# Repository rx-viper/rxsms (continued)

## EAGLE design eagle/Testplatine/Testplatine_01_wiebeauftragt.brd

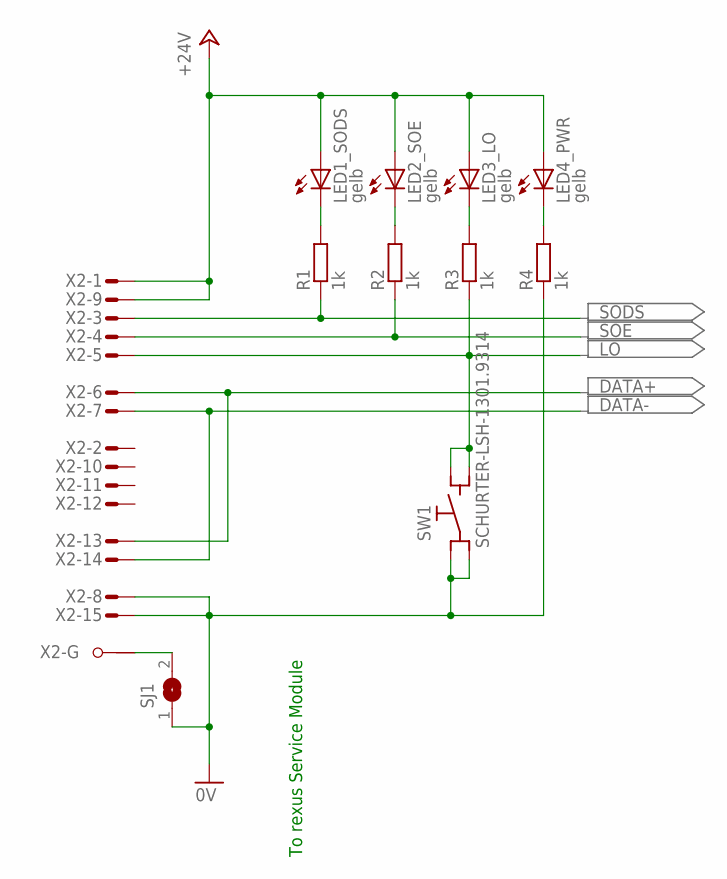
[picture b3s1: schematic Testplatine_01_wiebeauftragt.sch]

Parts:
LED1_SODS, LED2_SOE, LED3_LO, LED4_PWR: gelb; CHIPLED_0805
R1, R2, R3, R4: 1k; R0805
SJ1: SJ
SW1: SCHURTER-LSH-1301.9314; LSH
X2: M15HPS; M15HP

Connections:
0V: R4.1, SJ1.1, SW1.C1 (C), SW1.C2 (C), X2.8 (M), X2.15 (M)
+24V: LED1_SODS.A, LED2_SOE.A, LED3_LO.A, LED4_PWR.A, X2.1 (M), X2.9 (M)
DATA+: X2.6 (M), X2.13 (M)
DATA-: X2.7 (M), X2.14 (M)
LO: R3.1, SW1.NO1 (NO), SW1.NO2 (NO), X2.5 (M)
unnamed: LED1_SODS.C, R1.2
unnamed: LED2_SOE.C, R2.2
unnamed: LED3_LO.C, R3.2
unnamed: LED4_PWR.C, R4.2
unnamed: SJ1.2, X2.G1
SODS: R1.1, X2.3 (M)
SOE: R2.1, X2.4 (M)

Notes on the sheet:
To rexus Service Module

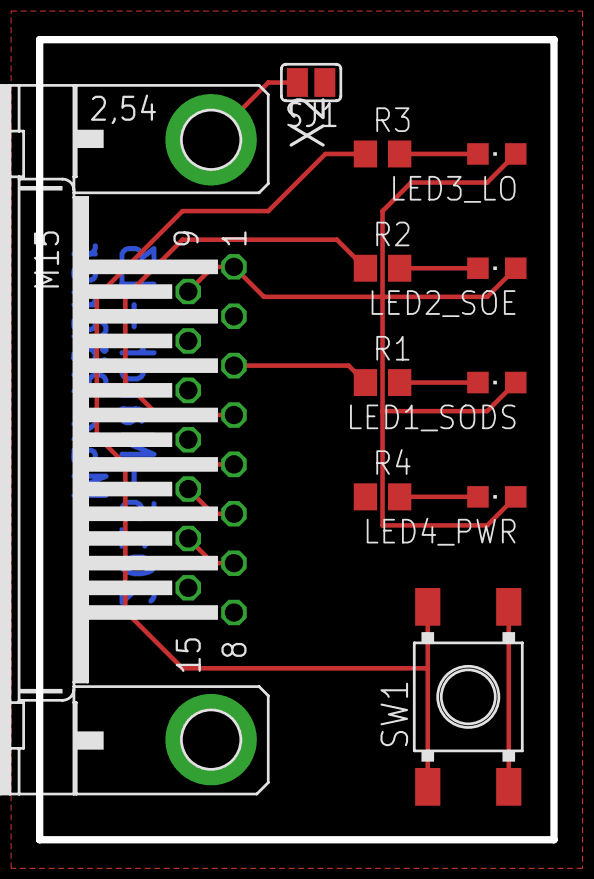
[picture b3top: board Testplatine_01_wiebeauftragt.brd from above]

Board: 2 copper layers, 28.6 x 44.5 mm, 11 parts (0 on the bottom side), 12 nets.

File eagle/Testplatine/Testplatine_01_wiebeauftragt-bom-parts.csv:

"Part";"Value";"Device";"Package";"Description";"MF";"MPN";"OC_FARNELL";"OC_NEWARK";"OC_RS";
"LED1_SODS";"gelb";"LEDCHIPLED_0805";"CHIPLED_0805";"LED";"";"";"2099242";"";"";
"LED2_SOE";"gelb";"LEDCHIPLED_0805";"CHIPLED_0805";"LED";"";"";"2099242";"";"";
"LED3_LO";"gelb";"LEDCHIPLED_0805";"CHIPLED_0805";"LED";"";"";"2099242";"";"";
"LED4_PWR";"gelb";"LEDCHIPLED_0805";"CHIPLED_0805";"LED";"";"";"2099242";"";"";
"R1";"1k";"R-EU_R0805";"R0805";"RESISTOR, European symbol";"";"";"1887280";"";"";
"R2";"1k";"R-EU_R0805";"R0805";"RESISTOR, European symbol";"";"";"1887280";"";"";
"R3";"1k";"R-EU_R0805";"R0805";"RESISTOR, European symbol";"";"";"1887280";"";"";
"R4";"1k";"R-EU_R0805";"R0805";"RESISTOR, European symbol";"";"";"1887280";"";"";
"SJ1";"";"SJ";"SJ";"SMD solder JUMPER";"";"";"";"";"";
"SW1";"SCHURTER-LSH-1301.9314";"SCHURTER-LSH-1301.9314";"LSH";"Schurter LSH Printmount Switches, Gullwing Leads [SMT]";"";"";"1217763";"";"";
"X2";"";"M15HPS";"M15HP";"SUB-D";"";"";"1097065 + 2x 1855027";"unknown";"692-7976 + 2x 719-9753";

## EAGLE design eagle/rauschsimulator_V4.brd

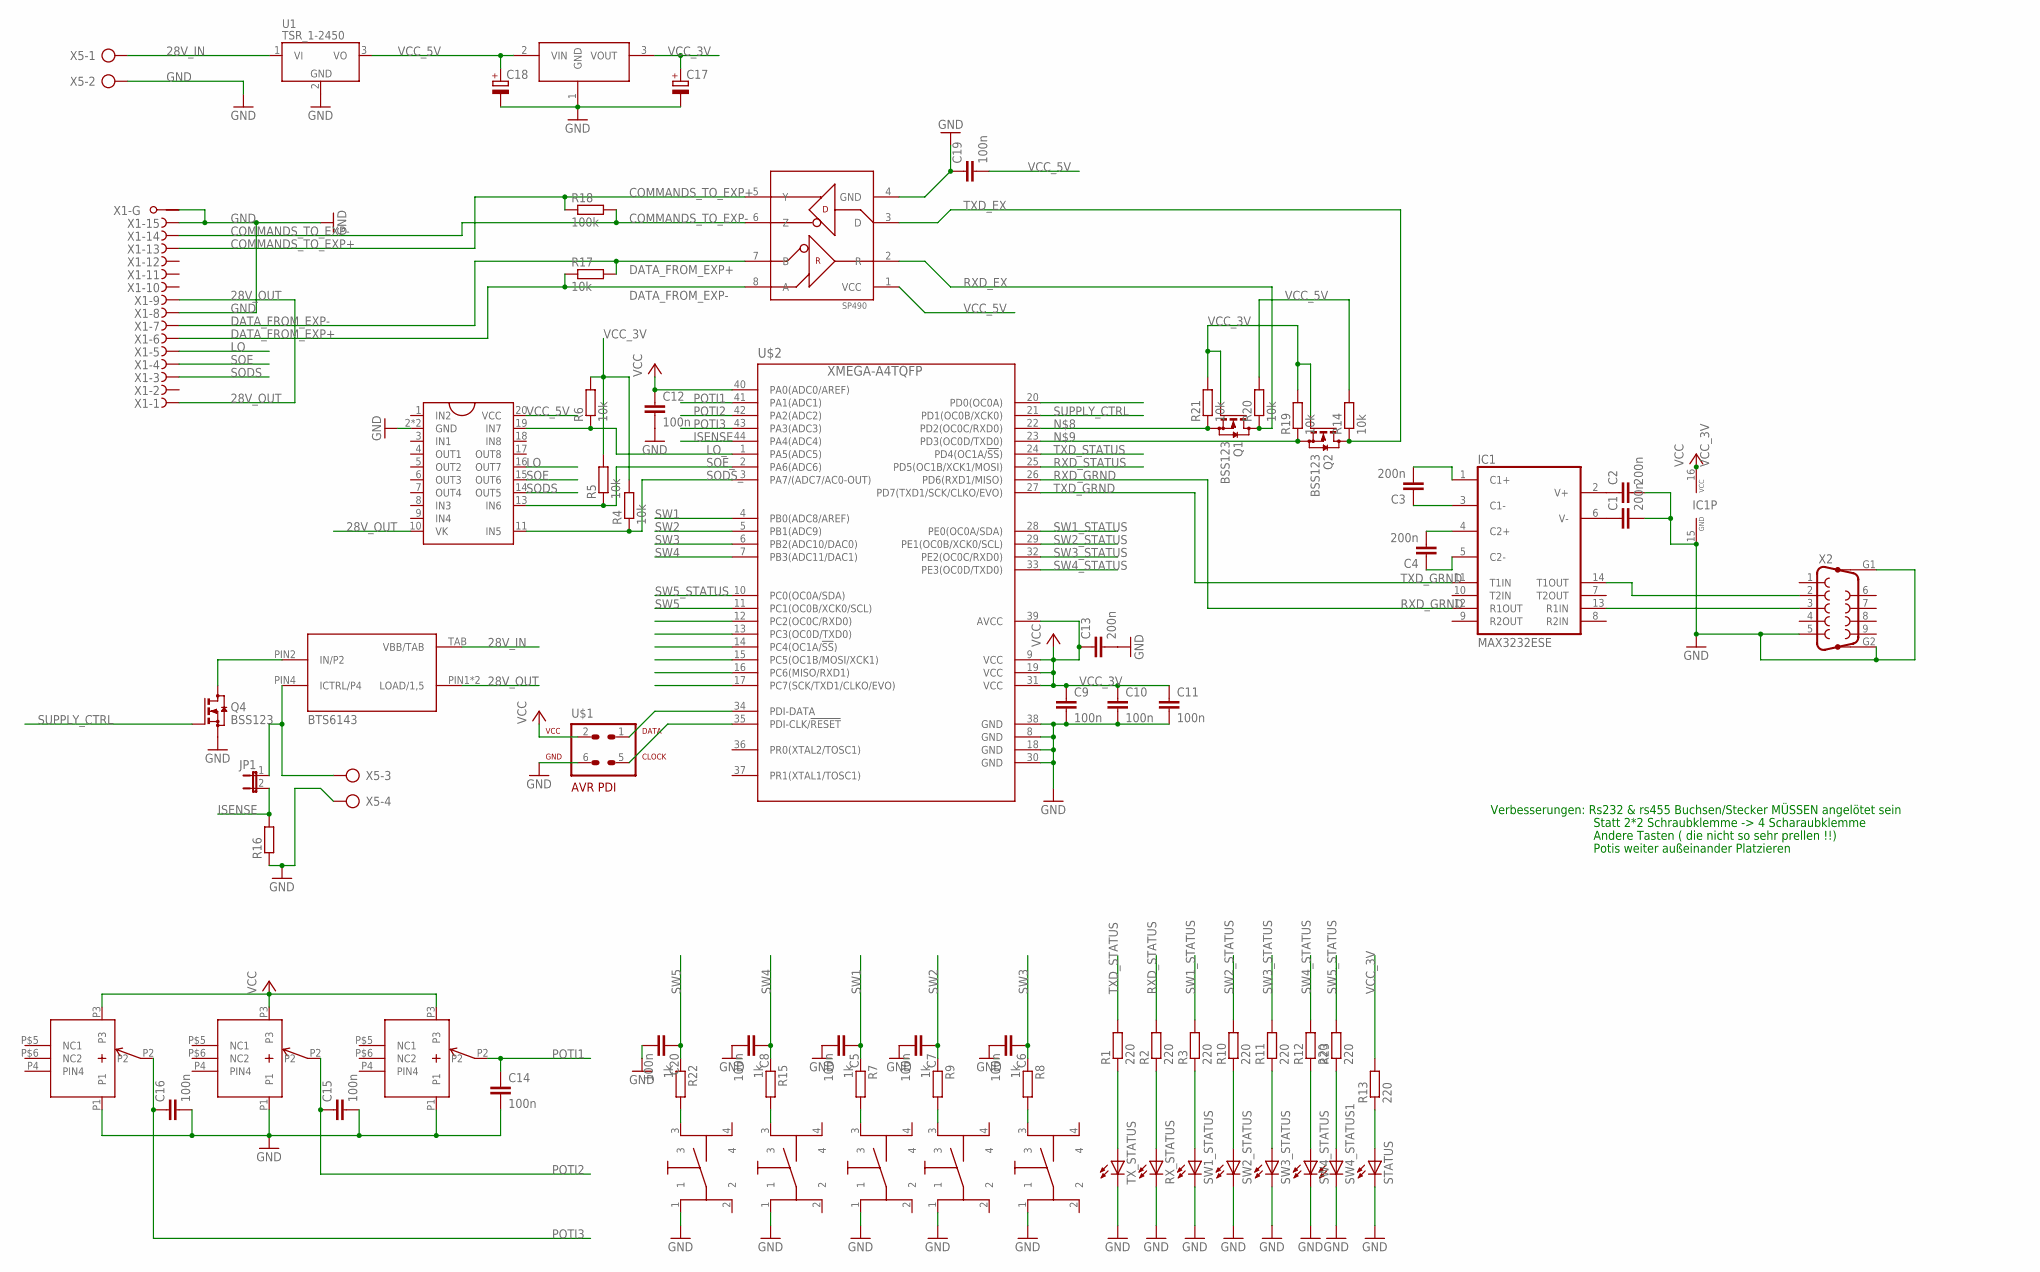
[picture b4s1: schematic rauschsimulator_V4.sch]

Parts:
C1, C2, C3, C4, C13: 200n; C0603K
C5, C6, C7, C8, C9, C10, C11, C12, C14, C15, C16, C19, C20: 100n; C0603K
C17, C18: CPOL-EUE2.5-6; E2,5-6
IC1: MAX3232ESE; SO16
JP1: JP1E; JP1
Q1, Q2, Q4: BSS123; SOT23
R1, R2, R3, R10, R11, R12, R13, R23: 220; R0603
R4, R5, R6, R14, R17, R19, R20, R21: 10k; R0603
R7, R8, R9, R15, R22: 1k; R0603
R16: R-EU_0617/22; 0617/22
R18: 100k; R0603
RX_STATUS: LEDCHIPLED_1206; CHIPLED_1206
STATUS: LEDCHIPLED_1206; CHIPLED_1206
SW1, SW2, SW3, SW4, SW5: SMS_IP67; IP67
SW1_STATUS, SW2_STATUS, SW3_STATUS, SW4_STATUS, SW4_STATUS1: LEDCHIPLED_1206; CHIPLED_1206
TX_STATUS: LEDCHIPLED_1206; CHIPLED_1206
U1: TSR_1-2450; TSR-1
U$1: AVR-PDIVERT; AVR-ISP-6
U$2: XMEGA-A4TQFP; TQFP44
U$3, U$4, U$5: STRK11K; VERT_POTI
U$13: LM1117; TO252
U$14: BTS6143; TO-252-5-1
U$15: UDN2596; DIL20
U$16: SP490; SO08
X1: F15HPS; F15HP
X2: F09HP
X5: AK500/4

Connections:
28V_IN: U1.1 (VI), U$14.TAB (VBB/TAB), X5.1
28V_OUT: U$14.PIN1 (LOAD/1,5), U$14.PIN5 (LOAD/1,5), U$15.10 (VK), X1.1 (F), X1.9 (F)
COMMANDS_TO_EXP+: R18.1, U$16.5 (Y), X1.13 (F)
COMMANDS_TO_EXP-: R18.2, U$16.6 (Z), X1.14 (F)
DATA_FROM_EXP+: R17.1, U$16.8 (A), X1.6 (F)
DATA_FROM_EXP-: R17.2, U$16.7 (B), X1.7 (F)
GND: C1.2, C2.2, C5.2, C6.2, C7.2, C8.2, C9.2, C10.2, C11.2, C12.2, C13.2, C14.2, C15.2, C16.2, C17.-, C18.-, C19.1, C20.2, IC1.15 (GND), Q4.2 (S), R16.1, RX_STATUS.C, STATUS.C, SW1.1, SW1_STATUS.C, SW2.1, SW2_STATUS.C, SW3.1, SW3_STATUS.C, SW4.1, SW4_STATUS.C, SW4_STATUS1.C, SW5.1, TX_STATUS.C, U1.2 (GND), U$1.6, U$2.8 (GND), U$2.18 (GND), U$2.30 (GND), U$2.38 (GND), U$3.P1, U$4.P1, U$5.P1, U$13.1 (GND), U$15.2 (GND), U$15.12 (GND), U$16.4 (GND), X1.8 (F), X1.15 (F), X1.G1, X2.5, X2.G1, X2.G2, X5.2, X5.4
ISENSE: JP1.2, R16.2, U$2.44 (PA4(ADC4))
LO: U$15.16 (OUT7), X1.5 (F)
LO_: R6.1, U$2.1 (PA5(ADC5)), U$15.19 (IN7)
unnamed: C1.1, IC1.6 (V-)
unnamed: C2.1, IC1.2 (V+)
unnamed: C4.2, IC1.4 (C2+)
unnamed: C4.1, IC1.5 (C2-)
unnamed: C3.1, IC1.3 (C1-)
unnamed: C3.2, IC1.1 (C1+)
unnamed: U$1.1, U$2.34 (PDI-DATA)
unnamed: Q1.2 (S), R21.1, U$2.22 (PD2(OC0C/RXD0))
unnamed: Q2.2 (S), R19.1, U$2.23 (PD3(OC0D/TXD0))
unnamed: IC1.13 (R1IN), X2.3
unnamed: R8.2, SW1.3
unnamed: IC1.14 (T1OUT), X2.2
unnamed: R9.2, SW2.3
unnamed: R7.2, SW3.3
unnamed: U$1.5, U$2.35 (PDI-CLK/!RESET)
unnamed: Q4.3 (D), U$14.PIN2 (IN/P2)
unnamed: R10.1, SW2_STATUS.A
unnamed: R1.1, TX_STATUS.A
unnamed: R2.1, RX_STATUS.A
unnamed: R3.1, SW1_STATUS.A
unnamed: R11.1, SW3_STATUS.A
unnamed: R12.1, SW4_STATUS.A
unnamed: R13.1, STATUS.A
unnamed: R15.2, SW4.3
unnamed: R23.1, SW4_STATUS1.A
unnamed: JP1.1, U$14.PIN4 (ICTRL/P4), X5.3
unnamed: R22.2, SW5.3
POTI1: C14.1, U$2.41 (PA1(ADC1)), U$5.P2
POTI2: C15.1, U$2.42 (PA2(ADC2)), U$4.P2
POTI3: C16.1, U$2.43 (PA3(ADC3)), U$3.P2
RXD_EX: Q1.3 (D), R20.1, U$16.2 (R)
RXD_GRND: IC1.12 (R1OUT), U$2.26 (PD6(RXD1/MISO))
RXD_STATUS: R2.2, U$2.25 (PD5(OC1B/XCK1/MOSI))
SODS: U$15.14 (OUT5), X1.3 (F)
SODS_: R4.1, U$2.3 (PA7/(ADC7/AC0-OUT)), U$15.11 (IN5)
SOE: U$15.15 (OUT6), X1.4 (F)
SOE_: R5.1, U$2.2 (PA6(ADC6)), U$15.13 (IN6)
SUPPLY_CTRL: Q4.1 (G), U$2.21 (PD1(OC0B/XCK0))
SW1: C5.1, R7.1, U$2.4 (PB0(ADC8/AREF))
SW1_STATUS: R3.2, U$2.28 (PE0(OC0A/SDA))
SW2: C7.1, R9.1, U$2.5 (PB1(ADC9))
SW2_STATUS: R10.2, U$2.29 (PE1(OC0B/XCK0/SCL))
SW3: C6.1, R8.1, U$2.6 (PB2(ADC10/DAC0))
SW3_STATUS: R11.2, U$2.32 (PE2(OC0C/RXD0))
SW4: C8.1, R15.1, U$2.7 (PB3(ADC11/DAC1))
SW4_STATUS: R12.2, U$2.33 (PE3(OC0D/TXD0))
SW5: C20.1, R22.1, U$2.11 (PC1(OC0B/XCK0/SCL))
SW5_STATUS: R23.2, U$2.10 (PC0(OC0A/SDA))
TXD_EX: Q2.3 (D), R14.1, U$16.3 (D)
TXD_GRND: IC1.11 (T1IN), U$2.27 (PD7(TXD1/SCK/CLKO/EVO))
TXD_STATUS: R1.2, U$2.24 (PD4(OC1A/!SS!))
VCC_3V: C9.1, C10.1, C11.1, C12.1, C13.1, C17.+, IC1.16 (VCC), Q1.1 (G), Q2.1 (G), R4.2, R5.2, R6.2, R13.2, R19.2, R21.2, U$1.2, U$2.9 (VCC), U$2.19 (VCC), U$2.31 (VCC), U$2.39 (AVCC), U$2.40 (PA0(ADC0/AREF)), U$3.P3, U$4.P3, U$5.P3, U$13.3 (VOUT)
VCC_5V: C18.+, C19.2, R14.2, R20.2, U1.3 (VO), U$13.2 (VIN), U$15.20 (VCC), U$16.1 (VCC)

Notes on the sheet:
BTS6143
Verbesserungen: Rs232 & rs455 Buchsen/Stecker MÜSSEN angelötet sein
Statt 2*2 Schraubklemme -> 4 Scharaubklemme
Andere Tasten ( die nicht so sehr prellen !!)
Potis weiter außeinander Platzieren

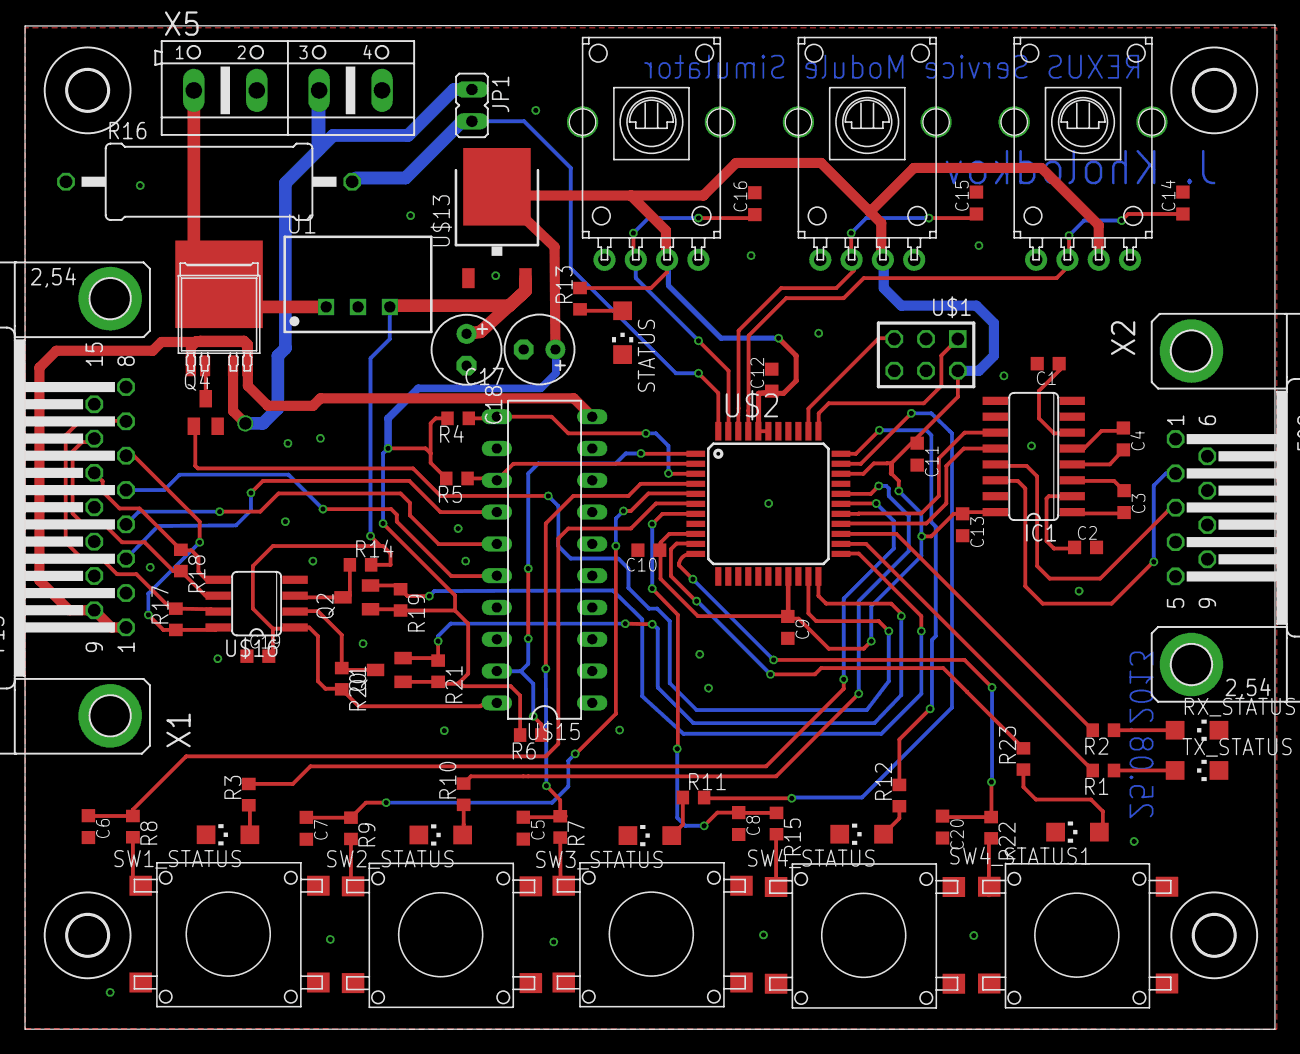
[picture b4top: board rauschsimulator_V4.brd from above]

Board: 2 copper layers, 99.8 x 80.2 mm, 78 parts (0 on the bottom side), 63 nets.

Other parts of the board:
U$6, U$7, U$8, U$10: 3,2

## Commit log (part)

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2014-04-28 Forschungsarbeit.pdf added
2014-08-30 added Makefile and prepare migration
2014-08-30 beautification: fixing various whitespace errors
2014-08-30 convert file line endings to native (unix) format
2014-08-31 migration to own init and adc implementation
2014-08-31 make clean now also deletes *.o files
2014-08-31 added BUGS file and instructions how to use avarice to debug the uC
2014-09-01 also cleanup the intermediate *.i and *.s files, if the --save-temps switch was set in the Makefile
2014-09-01 added scheduling and the button debounce task and RXSM CTRL interface task
2014-09-01 chmod -x from file
2014-09-22 removal of old legacy or non-license compatible code
2014-09-22 license change to GPLv3+
2014-09-22 directory structure simplified; dropped Atmel Studio files.
2014-10-31 migrate ADC sampling from background task to foreground
2014-10-31 minor cleanup
2014-10-31 refactor ADC sampling task
2014-10-31 debug task disable
2014-10-31 updated GDB config
2014-11-01 enabled ADC sample task
2014-11-01 fix sendrecv task
2014-11-02 disable -pedantic compiler warnings
2014-11-02 publish task_ctrl signal state
2014-11-02 initialize task only once
2014-11-02 refactor and add range check for ADC result
2014-11-03 bit error generation added
2014-11-03 implemented blocking of uplink/downlink
2014-11-17 wrapped line
2014-11-20 remove breakpoint from GDB config
2014-11-20 also switch on Error Inhibit LED using poti values
2014-11-21 switch to 8 slots and 200us complete cycle
2014-11-21 optimize scheduler
2014-11-28 disable DMA since it is not used
2015-02-13 deprecate nop() function since the builtin function is better
2015-02-14 split GPIO setup for groundstation and experiment side UART
2015-02-14 updated copyright notice
2015-02-14 refactor UART initialization
2015-02-14 fix misleading commit: byte is not dropped here yet
2015-02-15 rename total_bit_count -> stream_len_bytes and convert bits -> bytes
2015-02-15 make explicit that value is boolean only
2015-02-15 refactor bit error generation to separate task
2015-02-16 simplify by early exit of function
2015-02-16 fix wrong error pattern: flipped too many and wrong bits
2015-02-16 make Makefile compatible with newer avr-gcc 4.9.2
2015-02-16 fix: ignore error generation if inhibit button was toggled
2015-02-16 fix build errors due to partial variable renaming
2015-02-16 clearify comment
2015-02-16 update the UART status LEDs before sending instead of after receive
2015-02-16 simplify use of UART status LED
2015-02-16 put UART status LEDs code into single function and hide LED state/settings
2015-02-16 remove ignore_recv() function, too short for much content
2015-02-16 refactor byte drop generation to task_error
2015-02-17 simplify reception when uplink/gnd->exp is disabled after LO
2015-02-17 rename task_sample_adc_inputs to shorter task_adc
2015-02-17 fix year in copyright notice
2015-02-17 update indentation
2015-02-17 zero-set variable
2015-02-17 cleanup unused code and remainders from initial version and fovsuc project
2015-02-18 variables renamed
2015-02-18 allow other tasks/compilation units to see the slot lengths and number
2015-02-18 reduce width of hysteresis, ADCs are better than thought
2015-02-18 add space for the temperature measurement results
2015-02-18 condense reading and evaluating of the ADC values
2015-02-18 refactor partitioning and length mask generation
2015-02-20 add a variable when to start dropping bytes
2015-02-20 fix lost values because of 16bit shift
2015-02-20 generalize random number generation with mask
2015-02-20 improve bit error generator and documentstion
2015-02-20 rename variable
2015-02-20 increase hysteresis width because of too much noise
2015-02-20 rewrite function for sporadic communication drop
2015-02-20 rewrite function to update the error generators' settings
2015-02-24 user a form of 'drop' instead of 'block' to express the active dropping of bytes in the communication
2015-03-01 schematics for new HW
2015-03-01 add missing gafrc
2015-03-02 add connectors for two reserved UARTs
2015-03-02 add optional external crystal and capacitors
2015-03-02 update refdes attribute
2015-03-02 updated schematic PDFs
2015-03-02 WIP schematics and layout
2015-03-03 update comment
2015-03-03 continued schematics
2015-03-03 more files ignored
2015-03-03 added current schematics as PNGs
2015-03-03 added missing part library
2015-03-03 use polarized capacitors at in- and output of LD1117
2015-03-04 capacitors for isolating DCDC converter added
2015-03-04 add filter for TMV0505EN
2015-03-04 added optocouplers for MAX3232
2015-03-04 deleted lbr already present in eagle
2015-03-04 added RX EXP charging line to debug serial DSUB
2015-03-04 add push-button switch eagle lib
2015-03-04 second set of buttons and LEDs added
2015-03-04 add missing library for MAX3232
2015-03-04 replace schematic PNGs with single PDF
2015-03-05 add note that gEDA schematic is outdated
2015-03-05 progress on schematics
    * add of TVS supressor diodes for USB
    * add of RC-filter for USB
    * new library for light pipe
    * add of light-pipe to the schematics
    * add of pinheaders for two reserved UARTs
    * some resistors for LEDs updated, not final yet
2015-03-06 remove note/TODO; decide to use MLCC capacitor for LD1117
2015-03-06 reordered signals on uC
2015-03-06 add pinheaders for reserved ADC and GPIO pins
2015-03-06 minor cleanup, TODOs updated
2015-03-06 most components selected
    * replaced unregulated TMV regulator with TES3
    * added coil library
    * added missing coils to DCDC regulators
    * added various 100nF capacitors
    * added jumper between USB shield and RC filter
    * operate MAX3232 at 3.3V and use matching capacitors
2015-03-06 updated PDF of schematics
2015-03-09 selectively enable peripherals for each task
2015-03-09 add eagle library for schmitt trigger
2015-03-10 continued layout
2015-03-10 charging line and some extension headers added
2015-03-10 Design Rule file from manufaturer added
2015-03-11 filled top and bot
2015-03-11 added PDFs of schematics and layout
2015-03-12 added separate power supply board
2015-03-12 more OC_FARNELL added
2015-03-12 fix: use correct lib name for TEN 3-2410N DCDC iso regulator
2015-03-12 more OC added
2015-03-12 more finalization on the layout
2015-03-12 bom added
2015-03-12 Added logos, added ordering codes, otherwise minor changes
2015-03-12 added logos
2015-03-13 rename BOM files
2015-03-13 added OCs for 0 Ohm resistors
2015-03-13 exported pwr circuit schematics, board and BOM
2015-03-13 BOM for individual configurations added
2015-03-15 converted BOM file from XLS to ODS and added variants
2015-03-15 initial BOM for 19 main simulator PCBs total
2015-03-15 update old/discontinued schematics and layout
2015-03-16 port SW to rxsms-2.0-rc1 PCB
2015-03-16 update BOM's order codes, min. qty and qty intervals
2015-03-16 current BOM as CSV
2015-03-16 buy more switches so they get cheaper
2015-03-16 found a way to get remaining TEN 3-2410N regulators
2015-03-16 add labels on PCB for switches, potis and expansion headers
2015-03-16 add labels to DSUB connectors and screw terminal
2015-03-17 simplify objdump listings
2015-03-17 Revert "update old/discontinued schematics and layout"
    This reverts commit 747fb5a004a441a50f034454c07004aeee56455b.
2015-03-18 increase font size of button labels and LEDs
2015-03-18 add more traces to attach the experiment power FET to support the thermal
2015-03-21 refactor and fix ordering of ADC channels and attached potis
2015-03-23 FIX: Various important hardware fixes
    Several bugs in the PCB were found during soldering of the first rxsms-rc1
    PCB. This commit fixes these.
    o Add forgotten connection of VCC of NC7WZ17P6X schmitt-trigger and of
    bypass capacitor to actual VCC/3V3
    o Remove the 100k Ohm termination resitstor on SP490 output
    o Swap RS485 output and input wire pair on the REXUS experiment
2015-03-23 make label for V+/V- supply inputs also in the tStop layer
2015-03-23 update version's date on PCB
2015-03-25 allow SIM_LO pin to run in open drain (wired-and) configuration
2015-03-25 use the real SIM_LO value to update the LED
2015-03-25 cleanup
2015-03-25 fix LO default state
2015-03-26 fix ADC CH0 SCAN register value
2015-03-26 add simple task_debug implementation to dump raw ADC values
2015-03-26 increase resistor values for uplink/downlink and sim-pwr-led
2015-03-26 update resistors for LEDs
    - delete separate resistors for SMD and THT push buttons,
    use single footprint instead
    - update the /SIM_LO line routing
    - increase LED resistor values and order codes
2015-03-26 update date of PCB release
2015-03-26 added GPLv3 logo to PCB
2015-03-27 update order code of light pipe
2015-03-27 remove empty bmpxxxx layers
2015-03-27 update DRC
2015-03-27 several ordercodes updated
2015-03-27 some unneeded traces removed in favour of thermals
2015-03-27 ZARM logo slightly moved
2015-04-02 shifted polygon to make text more visible
2015-04-02 OC for 1k resistor updated
2015-04-02 OC for 270 ohm resistor updated
2015-04-02 OC for 4u7/50V capacitor updated
2015-04-02 fix prefix for coil
2015-04-02 updated TODO list, cleared OC update tasks
2015-04-09 minor beautification
    * mirrored reverse polarity schematics
    * some wires moved and a via inserted
2015-04-09 unify file names
2015-04-15 split connectors and screws and update ordercode
2015-04-15 update date/version info
2015-04-15 remove superflous polygon in GND plane
2015-04-15 update BOMs
2015-04-15 fix schematics and layout
    o add a dummy package (circle) to the screw. without package, it does not
    appear in the BOM
    o update the order code for the screw: new model is a bit longer but
    much cheaper which is important because of the high number of pieces.
    o synchronize/update the screws in the layout files
2015-04-24 renamed original per simulator BOM
2015-04-29 rename the BOM file for the first version's part order
2015-04-30 exported layout and schematics
2015-04-30 add missing order code to 1k resistor
2015-04-30 export layout as separate layers to PDF
2015-04-30 load library in project file
2015-04-30 cleanup: old and outdated gEDA files
2015-04-30 moved eagle lbr files to separate directory
2015-04-30 update project file to reflect changed library path
2015-05-08 fix OC for USB resistors
2015-05-08 make color and ordercode explicit for 4mm jacks
2015-05-08 move exported schematics and layout printouts to subdir
2015-05-08 assing value to 0 Ohm resistors
2015-05-08 updated date in PCB version
2015-05-08 reexport BOM from eagle
2015-05-21 update BOM
2015-05-26 highlight parts to add to manufactured PCBs
2015-06-03 add 'ok' for verified components
2015-06-03 add part list of variant for assembly
2015-08-05 add change records for first 2 completed PCBs
2015-08-05 add TODOs for SW: we could use table lookups instead of calculating the error probabilities/masks.
2015-08-21 also generate ASM listing files (*.lss) for each *.o file
2015-08-21 display relocations in objdump
2015-08-21 fix names for different versions of compiler/avrlibc
2015-08-22 use LUT for random values and masks
2015-08-22 move raw adc measurements to internal/file-local scope
2015-08-22 remove redundant check
2015-08-22 shorten 'triggered' struct member using bitfield
2015-08-22 simplify code
2015-08-22 cleanup and simplify code
2015-08-23 move error genration from task_adc to task_error
2015-08-23 add new Makefile rule 'program'
2015-08-23 add string representation of error tables
2015-08-23 isolate task_error_tables in separate .c file
    This step is necessary since otherwise we would get multiple defined symbols
    for each .c file that includes task_error_tables.h.
2015-08-23 globally init DMAC so tasks can use it
2015-08-23 print test string in task_debug via DMA
2015-08-23 print status info via task_debug
2015-08-24 use AES module for RNG
2015-08-24 simplify and shorten task_adc
2015-08-24 cleanup and use more C++ style comments
2015-08-24 beautify main.c
2015-08-26 beautify layout
2015-08-26 added more schematics and layouts as PDF
2015-08-26 forgot update of PDF after schematic were changed
2015-10-27 added change records for specific simulators
2018-07-24 Teileliste für Bestellung 07/2018 hinzugefügt
